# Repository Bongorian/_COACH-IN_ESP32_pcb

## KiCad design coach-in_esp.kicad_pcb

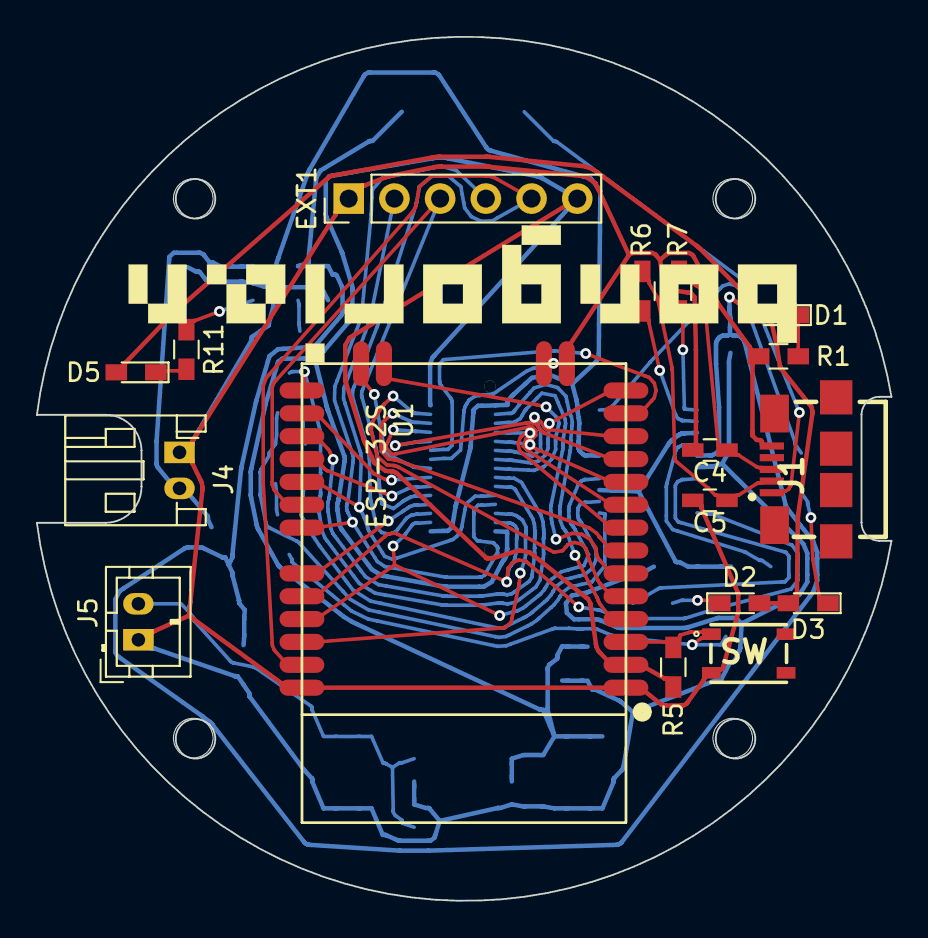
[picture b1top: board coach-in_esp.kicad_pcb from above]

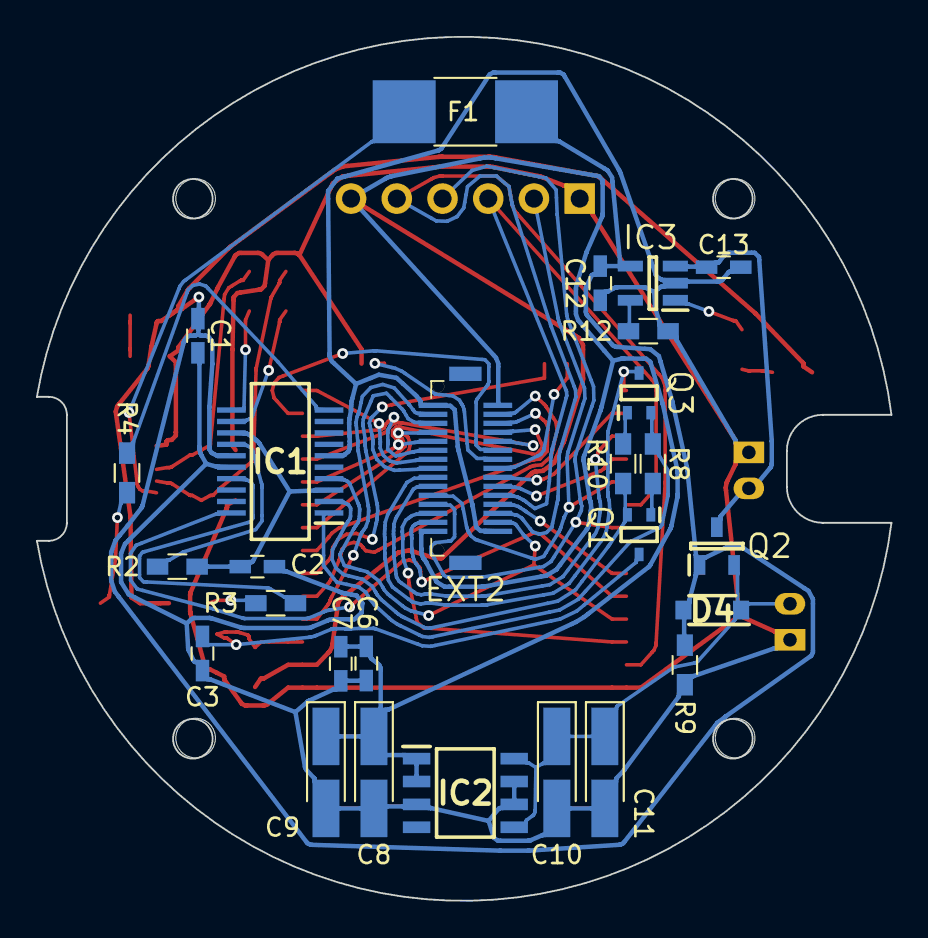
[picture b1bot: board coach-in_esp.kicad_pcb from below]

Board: 2 copper layers, 47.5 x 48.0 mm, 48 parts (27 on the bottom side), 51 nets.

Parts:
C1, C2: 0.1u; C_0603_HandSoldering
C3, C7: 100n; C_0603_HandSoldering
C4, C5: 47p; C_0603_HandSoldering
C6: 10u; C_0603_HandSoldering
C8, C9, C10, C11: 10u; CP_Tantalum_Case-A_EIA-3216-18_Hand
C12, C13: 4.7u; C_0603_HandSoldering
D1, D2, D3, D5: LED; LED_0603_HandSoldering
D4: RB160M-30TR; SODFL3516X90N
EXT1: Conn_01x06; Pin_Header_Straight_1x06_Pitch2.54mm
EXT2: EXT-2; DF123530DP05V86
F1: Fuse; R_1812_HandSoldering
IC1: FT231XS-R; SOP64P599X175-20N
IC2: LT1963AES8-3.3#PBF; SOIC127P599X175-8N
IC3: MCP73831T-2ATI_OT; SOT95P270X145-5N
J1: USB_CONN; ZX62-B-5PA(33)
J4: battery; JST_PH_S2B-PH-K_02x2.00mm_Angled
J5: EXT_VIN; JST_PH_B2B-PH-K_02x2.00mm_Straight
Q1, Q3: 2SC4081T106R; SOT65P210X90-3N
Q2: DMG3415U-7; SOT96P240X100-3N
R1, R3, R4, R6, R9, R11, R12: R; R_0603_HandSoldering
R2: 10K; R_0603_HandSoldering
R5, R8, R10: 10k; R_0603_HandSoldering
R7: 27; R_0603_HandSoldering
SW: SKRPACE010; SMT(4.2X3.2)
U1: ESP-32S
hole1, hole2, hole3, hole4: MountingHole_2.2mm_M2

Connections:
3V3OUT: C2.1, IC1.3, IC1.13, R2.1
+3V3: C6.1, C7.1, C8.1, C9.1, EXT1.6, EXT2.2, EXT2.29, IC2.1, IC2.2, R5.2, U1.2
CBUS1: IC1.17, R3.1
CBUS2: IC1.10, R4.1
D+: C4.1, J1.3, R7.1
D-: C5.1, J1.2, R6.1
DTR: IC1.1, Q3.2, R8.1
GND: C1.2, C2.2, C3.2, C4.2, C5.2, C6.2, C7.2, C8.2, C9.2, C10.2, C11.2, C12.2, C13.2, EXT1.1, EXT2.1, EXT2.30, IC1.6, IC1.16, IC2.3, IC2.6, IC2.7, IC3.2, J1.5, J4.1, J5.1, R1.1, R9.2, R12.2, SW.3, U1.1, U1.15, U1.38
IO0: EXT2.17, Q3.3, U1.25
IO2: EXT2.16, U1.24
IO4: EXT2.18, U1.26
IO5: EXT1.2, EXT2.21, U1.29
IO12: EXT2.13, U1.14
IO13: EXT2.14, U1.16
IO14: EXT2.12, U1.13
IO15: EXT2.15, U1.23
IO16: EXT2.19, U1.27
IO17: EXT2.20, U1.28
IO18: EXT1.3, EXT2.22, U1.30
IO19: EXT1.4, EXT2.23, U1.31
IO21: EXT2.24, U1.33
IO22: EXT2.25, U1.36
IO23: EXT1.5, EXT2.26, U1.37
IO25: EXT2.9, U1.10
IO26: EXT2.10, U1.11
IO27: EXT2.11, U1.12
IO32: EXT2.7, U1.8
IO33: EXT2.8, U1.9
IO34: EXT2.5, U1.6
IO35: EXT2.6, U1.7
unnamed: D1.1, R1.2
unnamed: D2.1, R3.2
unnamed: D3.1, R4.2
unnamed: D5.1, R11.1
unnamed: F1.2, J1.1
unnamed: IC1.11, R7.2
unnamed: IC1.12, R6.2
unnamed: IC3.1, R11.2
unnamed: IC3.5, R12.1
unnamed: Q1.1, R8.2
unnamed: Q3.1, R10.2
RES: IC1.14, R2.2
RESET: C3.1, Q1.3, R5.1, SW.1, U1.3
RTS: IC1.2, Q1.2, R10.1
RXD0: EXT2.27, IC1.20, U1.34
TXD0: EXT2.28, IC1.4, U1.35
VBAT: C13.1, IC3.3, J4.2, Q2.3
VBUS: C1.1, C12.1, D1.2, D2.2, D3.2, D4.2, D5.2, F1.1, IC1.15, IC3.4, Q2.1, R9.1
VIN: C10.1, C11.1, D4.1, IC2.5, IC2.8, J5.2, Q2.2
VN: EXT2.4, U1.5
VP: EXT2.3, U1.4

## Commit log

2018-06-26 init
